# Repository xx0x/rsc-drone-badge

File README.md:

# RSC Drone Badge

A badge (pendant) in the shape of FPV drone which I designed for my friends at [Resistance Support Club](http://resistance.support). The collective organizes soldering workshops, the collected money goes to Ukrainian defenders.

## BOM (Bill of Material)
<table>
    <tr>
        <th>Part</th>
        <th>Value</th>
        <th>Package</th>
        <th>Part number</th>
        <th>Qty</th>
    </tr>
    <tr>
        <td>IC1</td>
        <td>ATTINY</td>
        <td>DIP8</td>
        <td>ATTINY25V-10PU</td>
        <td>1</td>
    </tr>
    <tr>
        <td>LD1, LD2, LD3, LD4,<br>LD5, LD6, LD7, LD8,<br>LD9, LD10, LD11, LD12,<br>LD13, LD14, LD15, LD16</td>
        <td>Yellow LED</td>
        <td>5mm THT</td>
        <td>N0Y64L35,<br>L-53SYD</td>
        <td>16</td>
    </tr>
    <tr>
        <td>Q1, Q2, Q3, Q4</td>
        <td>BC547</td>
        <td>TO92</td>
        <td>BC547A/B/C</td>
        <td>4</td>
    </tr>
    <tr>
        <td>R1, R2, R3, R4</td>
        <td>10K</td>
        <td>0207</td>
        <td>CF1/4W-10K</td>
        <td>4</td>
    </tr>
    <tr>
        <td>R5, R6, R7, R8</td>
        <td>10R</td>
        <td>0207</td>
        <td>CF1/4W-10R</td>
        <td>4</td>
    </tr>
    <tr>
        <td>C1</td>
        <td>100n</td>
        <td>2.54 ceramic</td>
        <td>CC-100N</td>
        <td>1</td>
    </tr>
    <tr>
        <td>S1</td>
        <td>Tactile button</td>
        <td>6x6mm</td>
        <td>TACT-64K-F,<br>B3F-1020</td>
        <td>1</td>
    </tr>
    <tr>
        <td>BAT</td>
        <td>Battery holder</td>
        <td>CR2032</td>
        <td>DS1092-04-B6P</td>
        <td>1</td>
    </tr>
</table>

Then you just need a regular CR2032 battery and a 2 mm polypropylen, nylon or other string from your local store.

## Description

Custom designed PCB in Eagle, you can find both design files and gerber archive in the `pcb` subfolder. You can easily download the ZIP file with gerber and order the PCBs at your favorite PCB manufacturer. Recommended options are: Blue soldermask, ENIG surface.

The board contains ATtiny 25 MCU, you can find a precompiled HEX and shell upload script in `build` folder. Or you can compile it by yourself, eg. to run on another MCU like ATtiny 85. The source files are in the `code` folder, you'll need Arduino IDE with ATTinyCore for compiling them.

In `drawing` subfolder you can find board drawings in Adobe Illustrator format and a PDF with BOM and build instructions.

Слава Україні! 🇺🇦

## Mini Variant

The directories also contain a simplified variant, smaller with 4 LEDs.

## License

MIT, feel free to share!

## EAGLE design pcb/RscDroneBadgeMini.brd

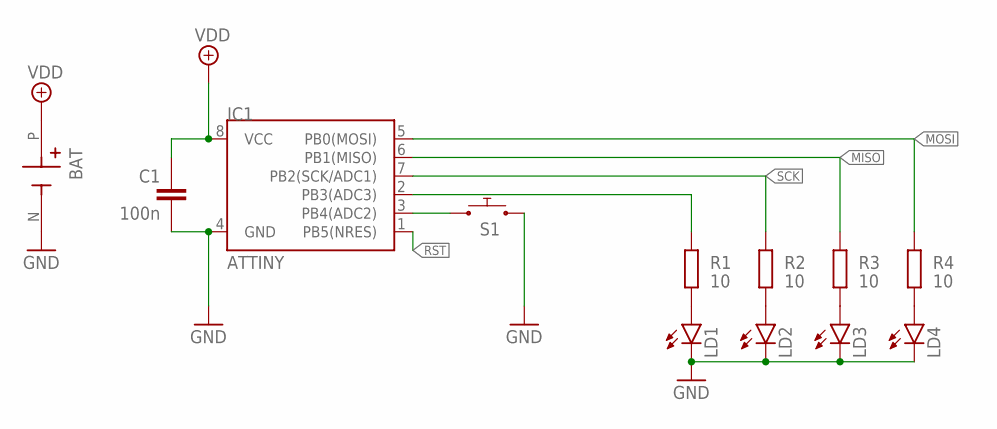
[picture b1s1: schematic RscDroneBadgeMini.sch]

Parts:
BAT: CR2032; CR2032_PLASTIC
C1: 100n; C_2.54
IC1: ATTINY; DIL08
LD1, LD2, LD3, LD4: LED_THT-5MM_NICE; LED_5MM_NICE
R1, R2, R3, R4: 10; RCL_0207
S1: 6x6mm BUTTON; TACTILE-PTH

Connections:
GND: BAT.N (NEG), C1.2, IC1.4 (GND), LD1.K (C), LD2.K (C), LD3.K (C), LD4.K (C), S1.3 (2), S1.4 (2)
MISO: IC1.6 (PB1(MISO)), R3.2
MOSI: IC1.5 (PB0(MOSI)), R4.2
unnamed: IC1.3 (PB4(ADC2)), S1.1, S1.2 (1)
unnamed: LD1.A, R1.1
unnamed: LD2.A, R2.1
unnamed: LD3.A, R3.1
unnamed: LD4.A, R4.1
unnamed: IC1.2 (PB3(ADC3)), R1.2
RST: IC1.1 (PB5(NRES))
SCK: IC1.7 (PB2(SCK/ADC1)), R2.2
VDD: BAT.P (POS), C1.1, IC1.8 (VCC)

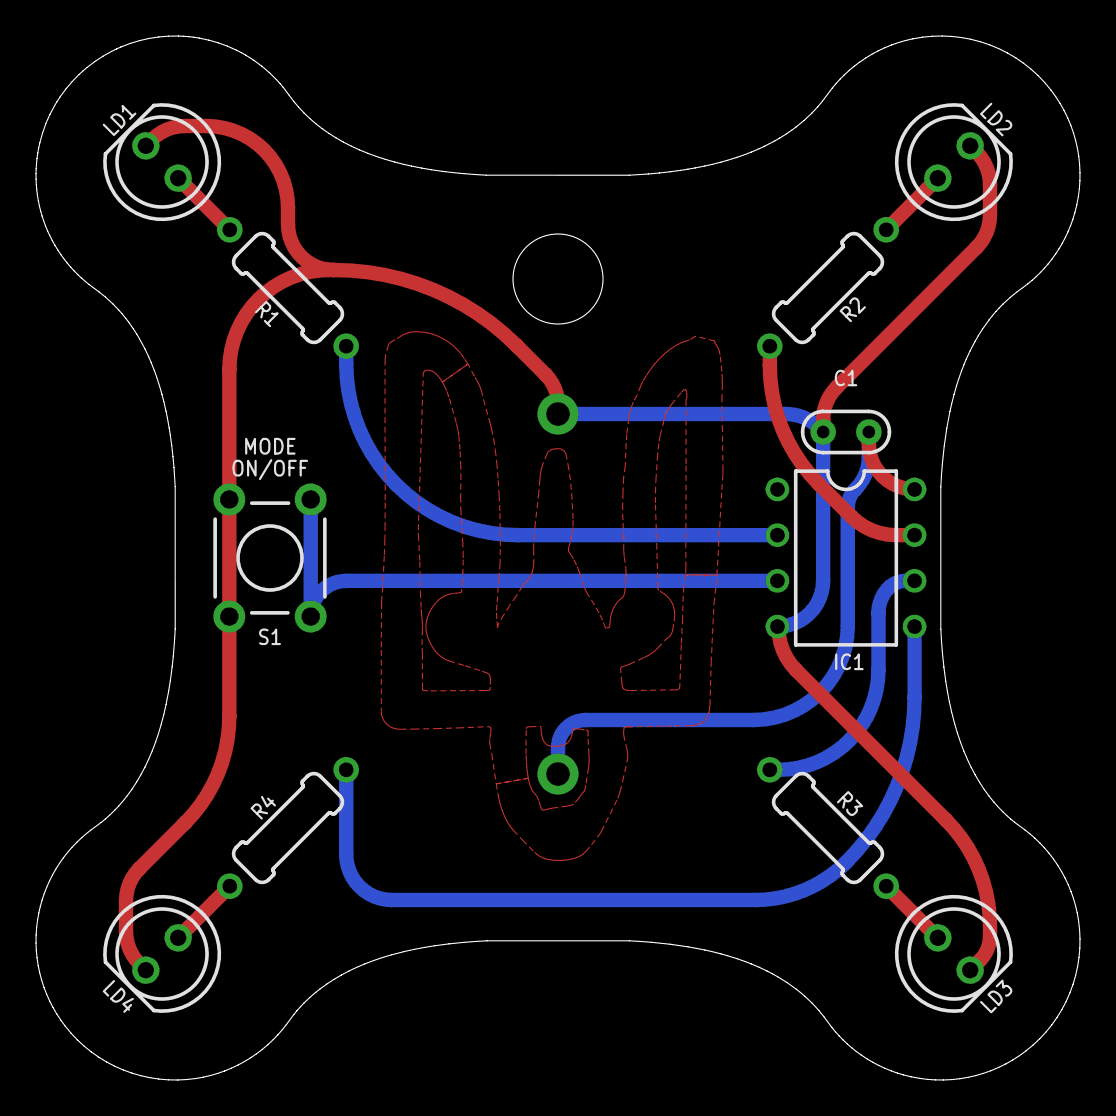
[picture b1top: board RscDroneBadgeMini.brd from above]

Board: 2 copper layers, 58.0 x 58.0 mm, 12 parts (1 on the bottom side), 11 nets.

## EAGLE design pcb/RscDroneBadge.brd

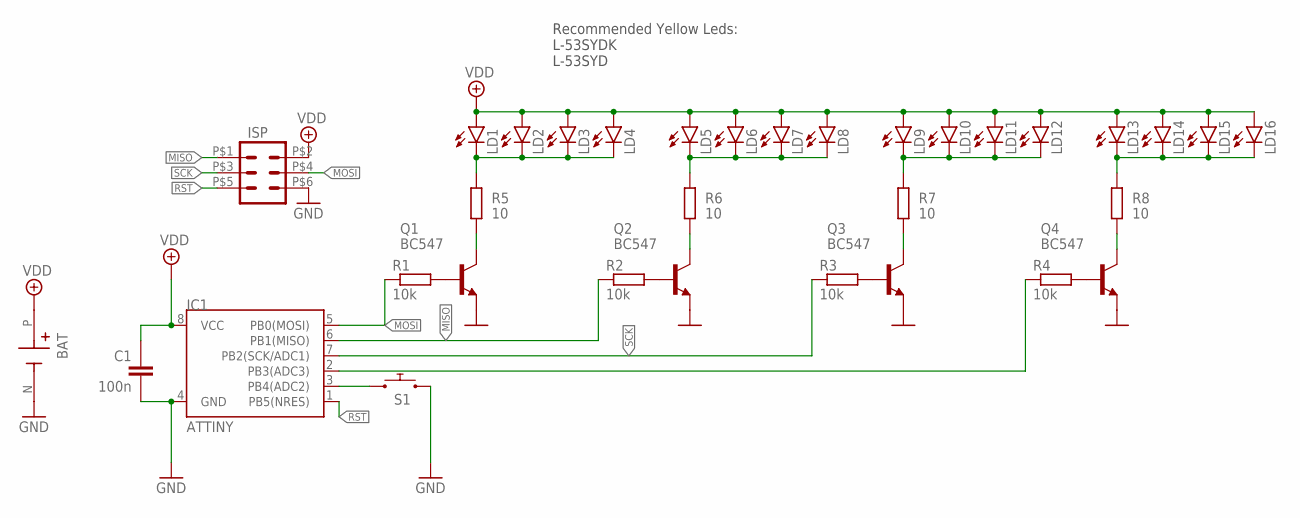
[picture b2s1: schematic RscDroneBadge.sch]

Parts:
BAT: CR2032 HOLDER; CR2032_PLASTIC
C1: 100n; C_2.54
IC1: ATTINY; DIL08
ISP: 2X3POGONO_VIA; 2X3_POGO_NO_VIA
LD1, LD2, LD3, LD4, LD5, LD6, LD7, LD8, LD9, LD10, LD11, LD12, LD13, LD14, LD15, LD16: LED_THT-5MM_NICE; LED_5MM_NICE
Q1, Q2, Q3, Q4: BC547; TO92_ROUND
R1, R2, R3, R4: 10k; RCL_0207
R5, R6, R7, R8: 10; RCL_0207
S1: 6x6mm BUTTON; TACTILE-PTH

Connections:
GND: BAT.N (NEG), C1.2, IC1.4 (GND), ISP.P$6 (6), Q1.1 (E), Q2.1 (E), Q3.1 (E), Q4.1 (E), S1.3 (2), S1.4 (2)
MISO: IC1.6 (PB1(MISO)), ISP.P$1 (1), R2.1
MOSI: IC1.5 (PB0(MOSI)), ISP.P$4 (4), R1.1
unnamed: IC1.3 (PB4(ADC2)), S1.1, S1.2 (1)
unnamed: Q1.2 (B), R1.2
unnamed: Q2.2 (B), R2.2
unnamed: Q3.2 (B), R3.2
unnamed: Q4.2 (B), R4.2
unnamed: IC1.2 (PB3(ADC3)), R4.1
unnamed: Q1.3 (C), R5.1
unnamed: Q2.3 (C), R6.1
unnamed: Q3.3 (C), R7.1
unnamed: Q4.3 (C), R8.1
unnamed: LD9.K (C), LD10.K (C), LD11.K (C), LD12.K (C), R7.2
unnamed: LD13.K (C), LD14.K (C), LD15.K (C), LD16.K (C), R8.2
unnamed: LD5.K (C), LD6.K (C), LD7.K (C), LD8.K (C), R6.2
unnamed: LD1.K (C), LD2.K (C), LD3.K (C), LD4.K (C), R5.2
RST: IC1.1 (PB5(NRES)), ISP.P$5 (5)
SCK: IC1.7 (PB2(SCK/ADC1)), ISP.P$3 (3), R3.1
VDD: BAT.P (POS), C1.1, IC1.8 (VCC), ISP.P$2 (2), LD1.A, LD2.A, LD3.A, LD4.A, LD5.A, LD6.A, LD7.A, LD8.A, LD9.A, LD10.A, LD11.A, LD12.A, LD13.A, LD14.A, LD15.A, LD16.A

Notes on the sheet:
Recommended Yellow Leds: L-53SYDK L-53SYD

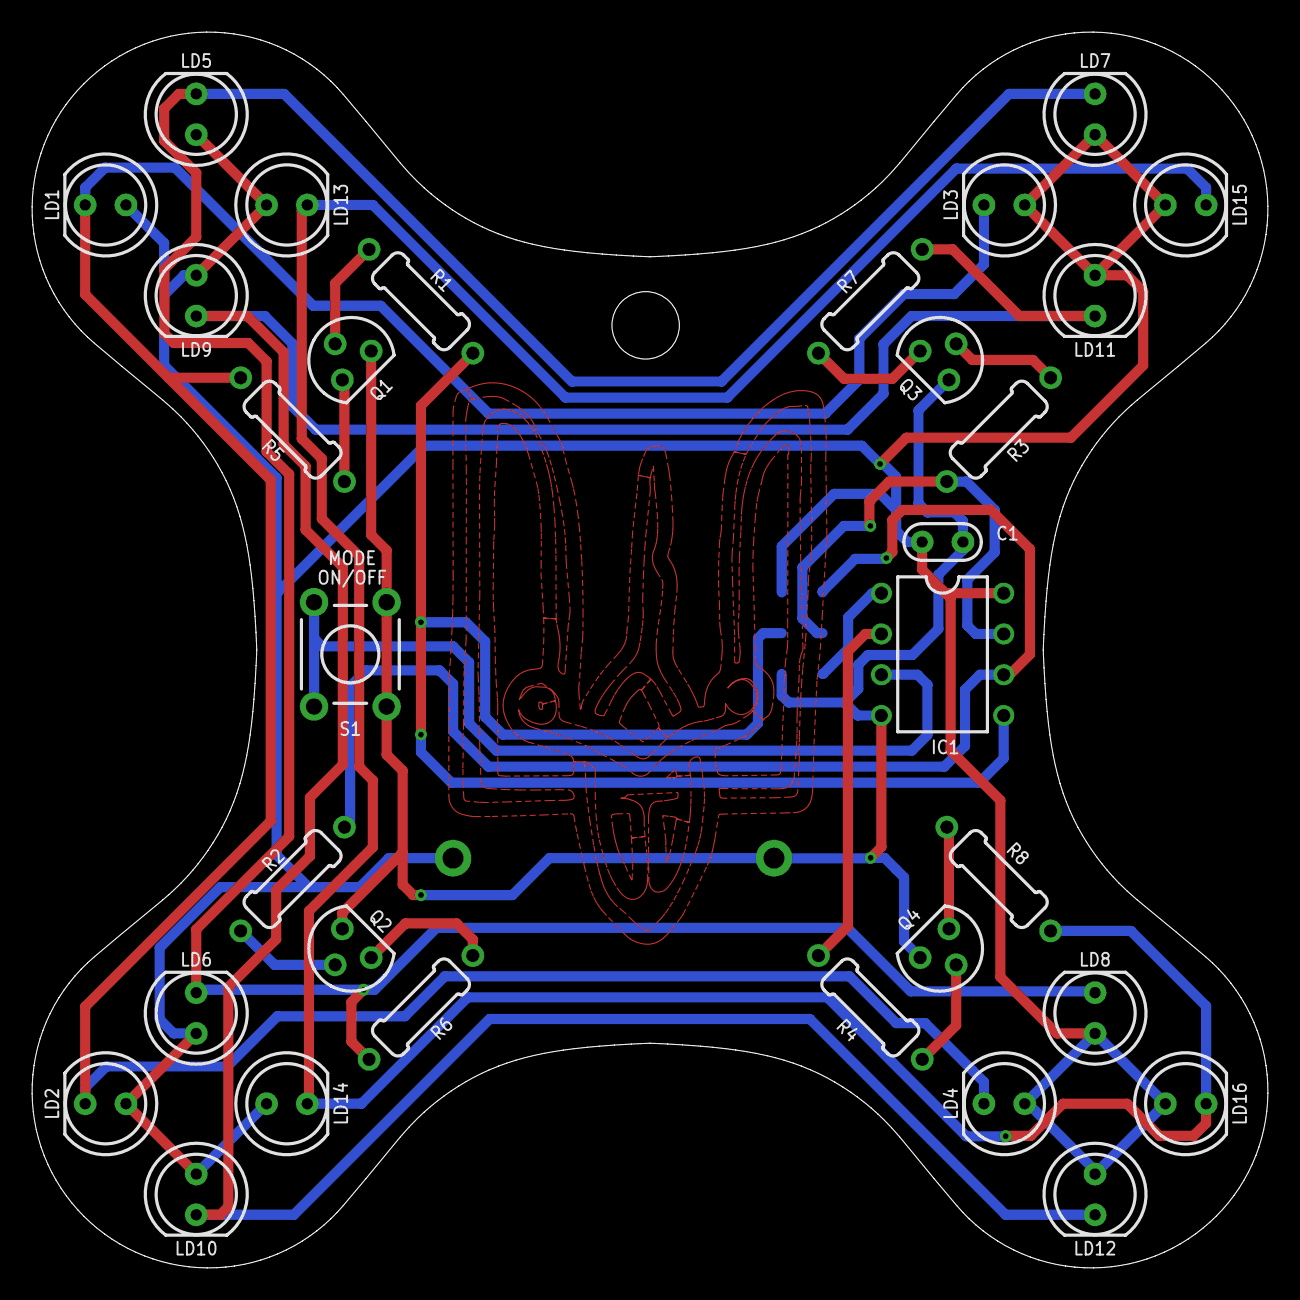
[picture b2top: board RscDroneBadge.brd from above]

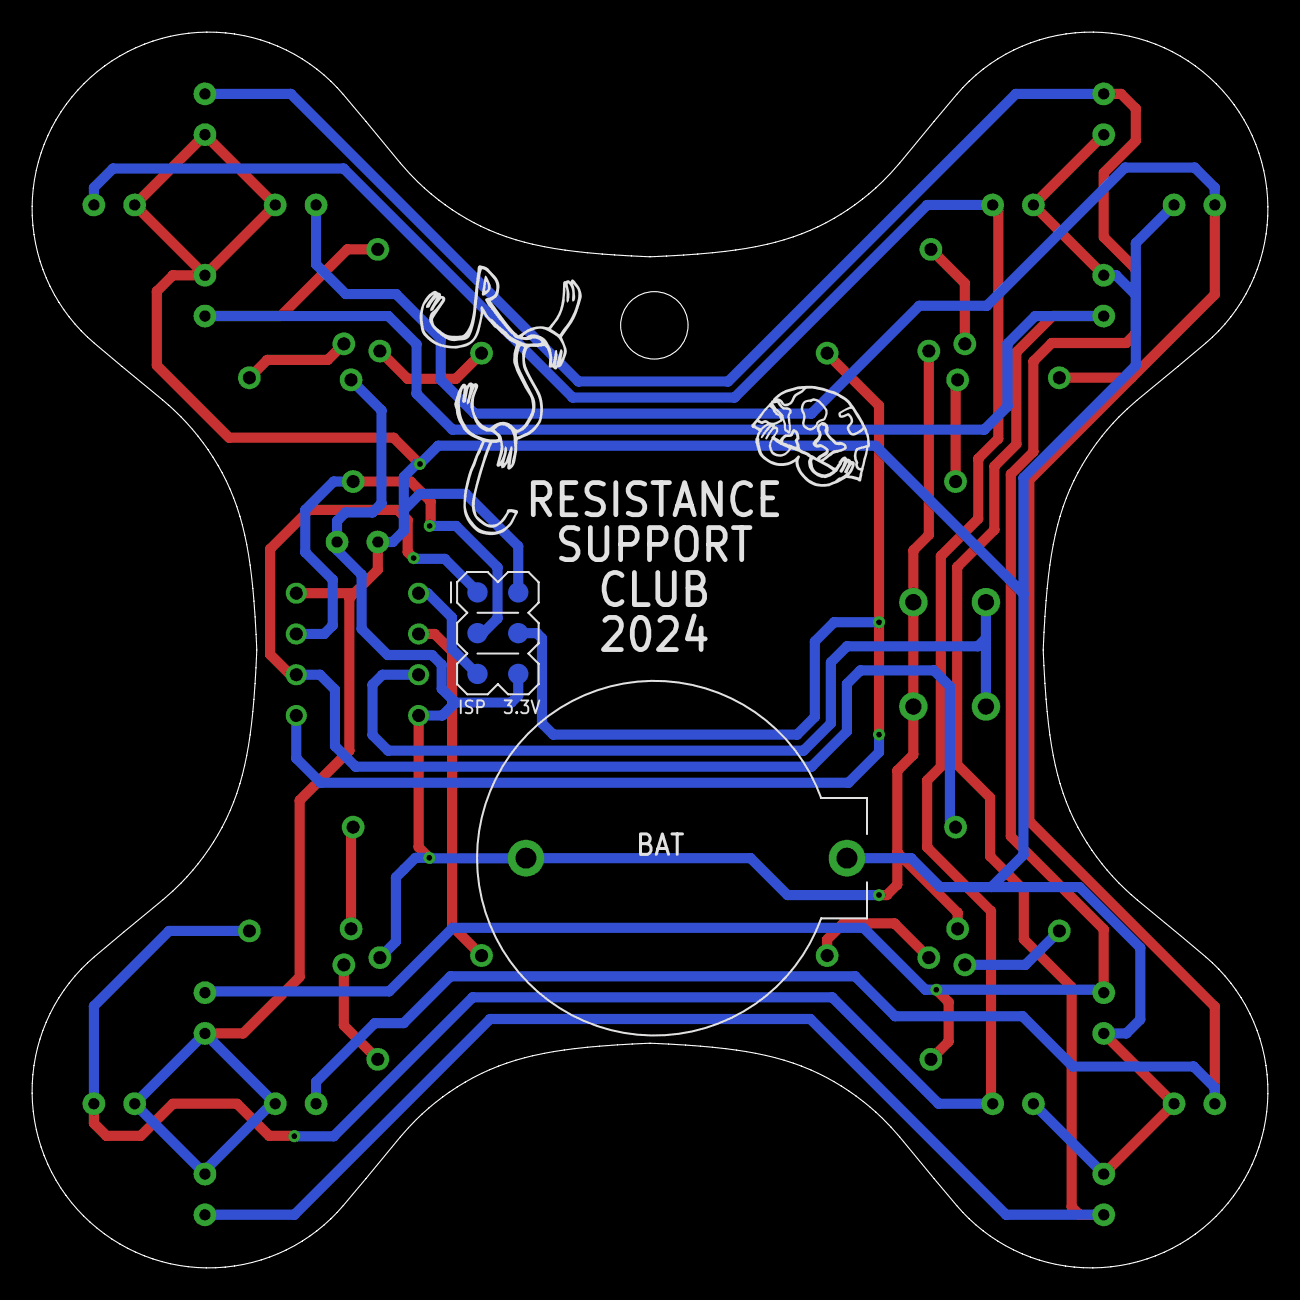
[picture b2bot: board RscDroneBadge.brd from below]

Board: 2 copper layers, 77.0 x 77.0 mm, 33 parts (2 on the bottom side), 20 nets.

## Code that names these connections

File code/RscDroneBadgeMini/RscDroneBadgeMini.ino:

/**
 * Code for RSC DRONE BADGE (Mini Variant with 4 LEDs)
 * MCU: ATTINY25 @ 8 MHz
 * Using: Arduino + ATTinyCore
 * Author: Vaclav M (github.com/xx0x)
 * Licence: MIT
 */

#include <avr/interrupt.h>
#include <avr/sleep.h>

// LED configuration
#define LEDS 4
const uint8_t ledPinsFast[LEDS] = {PB0, PB1, PB3, PB2};

#define SET_STATE_HIGH(pin_name) (PORTB |= (1 << pin_name))
#define SET_STATE_LOW(pin_name) (PORTB &= ~(1 << pin_name))
#define SET_STATE(pin_name, state) ((state) ? SET_STATE_HIGH(pin_name) : SET_STATE_LOW(pin_name))

#define PIN_BUTTON 4
#define BUTTON_PRESSED LOW

#define INTERVAL_NORMAL 250
#define INTERVAL_FAST 100
#define TURN_OFF_INTERVAL 1000

// Animations
uint8_t animationType = 0;          // current animation
uint8_t animationFrame = 0;         // current animation frame
uint8_t animationEnabled = 1;       // whether animations enabled
uint8_t animationInterval = INTERVAL_NORMAL; // interval between animation frames

// Button state tracking
uint8_t buttonPressed = 0;       
uint8_t modeChangeDisabled = 0;

// Timing variables
unsigned long lastTime = 0;
unsigned long lastTimeButton = 0;

// LED states
uint8_t leds[LEDS];

// Animation defines
#define ANIMATIONS 11
#define ANIMATION_RANDOM 10
uint8_t randomAnimation = 1;
uint8_t randomFramesCounter = 0;

// Forward declarations
void animate(void);
void updateLeds(void);
void sleep(void);
void animationOff(void);

void setup() {
  // Set LED pins as outputs
  DDRB |= ((1 << PB0) | (1 << PB1) | (1 << PB2) | (1 << PB3));
  
  // Set button pin as input with pullup
  pinMode(PIN_BUTTON, INPUT_PULLUP);
}

void loop() {
  // Debounce to prevent double taps
  if (millis() - lastTimeButton > 200) {
    if (digitalRead(PIN_BUTTON) == BUTTON_PRESSED) {
      if (!buttonPressed) {
        buttonPressed = 1;
        lastTimeButton = millis();
      }
      // Check whether to sleep
      if (lastTimeButton && (millis() - lastTimeButton > TURN_OFF_INTERVAL)) {
        animationOff();
        animationEnabled = 0;
        updateLeds();
        delay(200);
        sleep();
        lastTimeButton = 0;
        animationEnabled = 1;
        modeChangeDisabled = 1;
      }
    } else {
      lastTimeButton = 0;
      
      // If mode released, change mode
      if (buttonPressed) {
        if (!modeChangeDisabled) {
          lastTime = 0;
          animationType = (animationType + 1) % ANIMATIONS;
          animationFrame = 0;
        }
        modeChangeDisabled = 0;
        lastTimeButton = millis();
      }
      buttonPressed = 0;
    }
  }

  // Handle animation and update LEDs
  if (animationEnabled) {
    // Check if it's time for a new animation frame
    if (millis() - lastTime >= animationInterval) {
      lastTime = millis();
      animate();
    }
    updateLeds();
  }
}

// Empty interrupt handler
ISR(PCINT0_vect) {}

void sleep() {
  GIMSK |= _BV(PCIE);                  // Enable Pin Change Interrupts
  PCMSK |= _BV(PCINT4);                // Use PB4 as interrupt pin
  ADCSRA &= ~_BV(ADEN);                // ADC off
  set_sleep_mode(SLEEP_MODE_PWR_DOWN);
  sleep_enable();
  sei();
  sleep_cpu();

  // Wake up
  cli();
  PCMSK &= ~_BV(PCINT4);
  sleep_disable();
  ADCSRA |= _BV(ADEN);
  sei();

  // Check if button is still pressed for 1s
  for (uint8_t i = 0; i < 4; i++) {
    delay(250);
    if (digitalRead(PIN_BUTTON) != BUTTON_PRESSED) {
      sleep();
      break;
    }
  }
}

void animate() {
  animationInterval = INTERVAL_NORMAL;
  uint8_t animationTypeNow = animationType;
  
  // Handle random animation selection
  if (animationTypeNow == ANIMATION_RANDOM) {
    if (++randomFramesCounter > 8) {
      uint8_t x;
      do {
        x = (rand() % 7) + 1;
      } while (x == randomAnimation);
      randomAnimation = x;
      randomFramesCounter = 0;
      animationFrame = 0;
    }
    animationTypeNow = randomAnimation;
  }

  // Reset all LEDs first
  animationOff();

  // Set animation speed
  if (animationTypeNow == 3 || animationTypeNow == 5 || 
      animationTypeNow == 7 || animationTypeNow == 9) {
    animationInterval = INTERVAL_FAST;
    animationTypeNow--; // Use the same pattern as the slower version
  }

  // Handle different animation patterns
  switch (animationTypeNow) {
    case 0: // All on
      for (uint8_t i = 0; i < LEDS; i++) leds[i] = 1;
      break;
      
    case 1: // All blink
      animationFrame ^= 1; // Toggle between 0 and 1
      if (animationFrame) {
        for (uint8_t i = 0; i < LEDS; i++) leds[i] = 1;
      }
      break;
      
    case 2: // Left-right
      animationFrame = (animationFrame + 1) % 2;
      leds[animationFrame] = 1;
      leds[animationFrame + 2] = 1;
      break;
      
    case 4: // Up-down
      animationFrame = (animationFrame + 1) % 2;
      if (animationFrame == 0) {
        leds[0] = leds[3] = 1;
      } else {
        leds[1] = leds[2] = 1;
      }
      break;
      
    case 6: // Rotate
      animationFrame = (animationFrame + 1) % LEDS;
      leds[(animationFrame == 0) ? 0 : (animationFrame == 1) ? 2 : (animationFrame == 2) ? 3 : 1] = 1;
      break;
      
    case 8: // Rotate backwards
      animationFrame = (animationFrame + 1) % LEDS;
      leds[(animationFrame == 0) ? 1 : (animationFrame == 1) ? 3 : (animationFrame == 2) ? 2 : 0] = 1;
      break;
  }
}

void animationOff() {
  for (uint8_t i = 0; i < LEDS; i++) {
    leds[i] = 0;
  }
}

void updateLeds() {
  for (uint8_t i = 0; i < LEDS; i++) {
    SET_STATE(ledPinsFast[i], leds[i]);
  }
}

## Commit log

2024-03-29 add code (ugly but working)
2024-03-29 work in progress
2024-03-29 update schematic and board, add drawing
2024-03-29 alignment fix
2024-03-30 routing
2024-03-31 finishing
2024-04-09 code update
2024-05-01 add manual and drawings
2024-05-08 add manual print file
2024-05-08 basic PWM working
2024-05-08 add random animation
2024-05-08 update manual print
2024-05-08 fix debounce, add upload script
2024-06-16 add code comments
2024-06-16 add windows upload script
2024-08-27 fix readme
2024-08-27 remove "85" from ATTINY label on the board
2024-08-27 remove old gerber
2024-08-27 add BOM to readme
2024-08-27 update string info
2024-11-01 add a4 manual
2024-12-07 add attiny85 build (same code)
2024-12-08 add "mini" variant of the badge
2024-12-08 silkscreen fixes
2025-05-30 add "mini" variant
2025-06-02 add mini manual and update the large version manual
